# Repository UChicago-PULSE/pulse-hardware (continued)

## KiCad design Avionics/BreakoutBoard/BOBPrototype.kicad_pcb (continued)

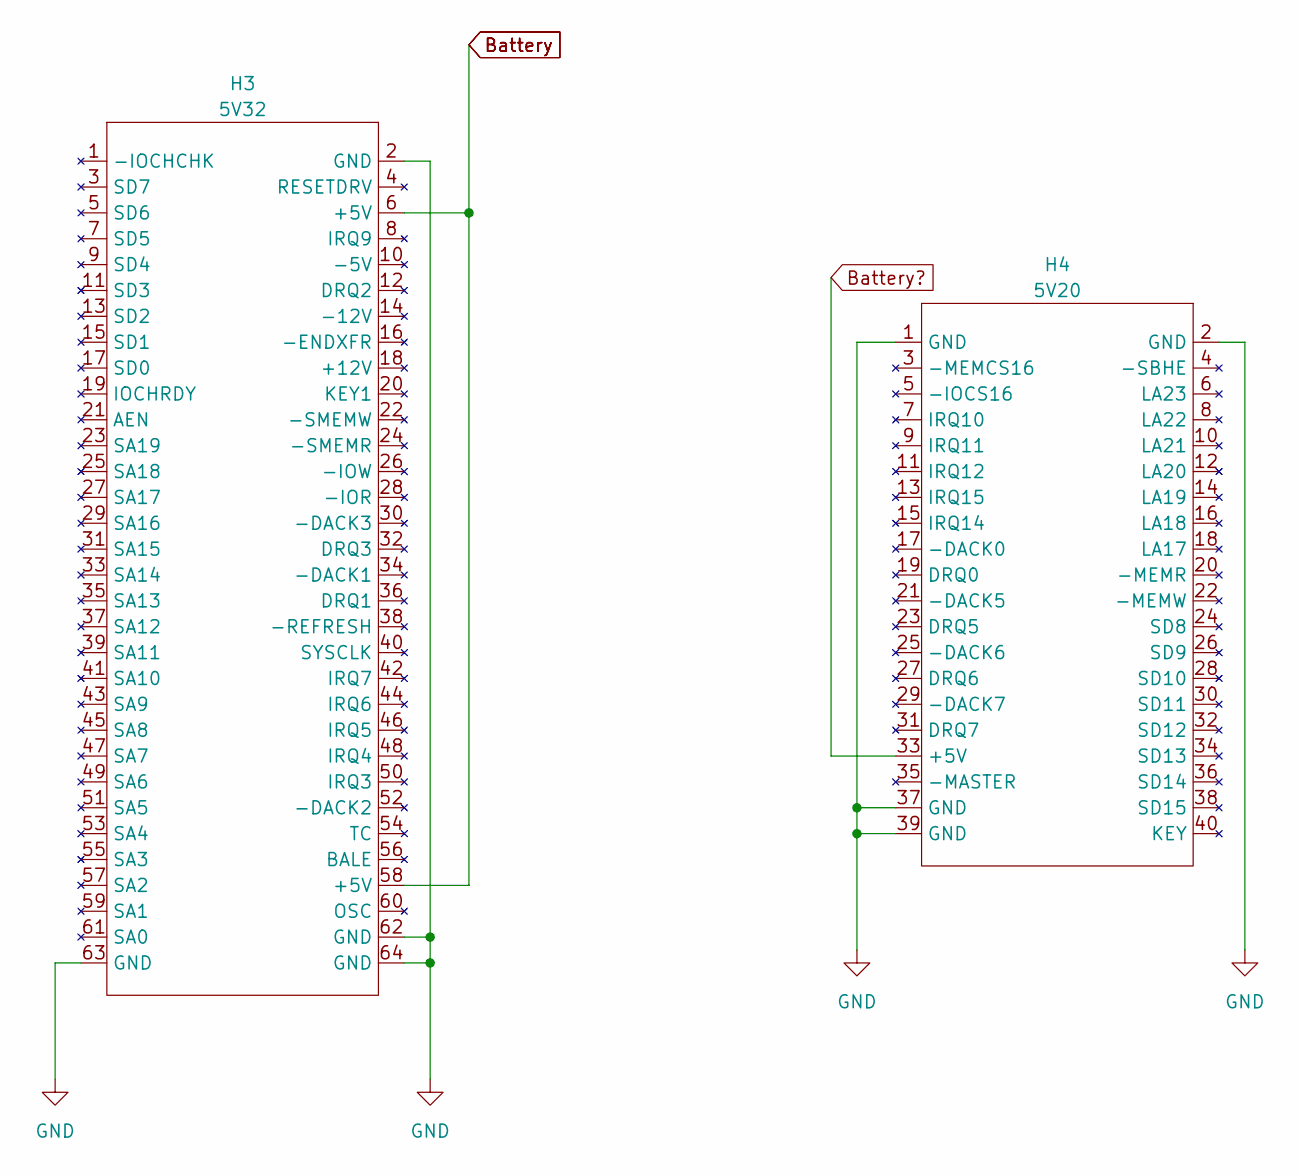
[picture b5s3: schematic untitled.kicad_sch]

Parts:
H3: 5V32
H4: 5V20

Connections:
Battery: H3.6 (+5V), H3.58 (+5V)
Battery?: H4.33 (+5V)
GND: H3.2 (GND), H3.62 (GND), H3.63 (GND), H3.64 (GND), H4.1 (GND), H4.2 (GND), H4.37 (GND), H4.39 (GND); also elsewhere on the board

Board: 2 copper layers, 9 parts (0 on the bottom side), 68 nets, no tracks yet.

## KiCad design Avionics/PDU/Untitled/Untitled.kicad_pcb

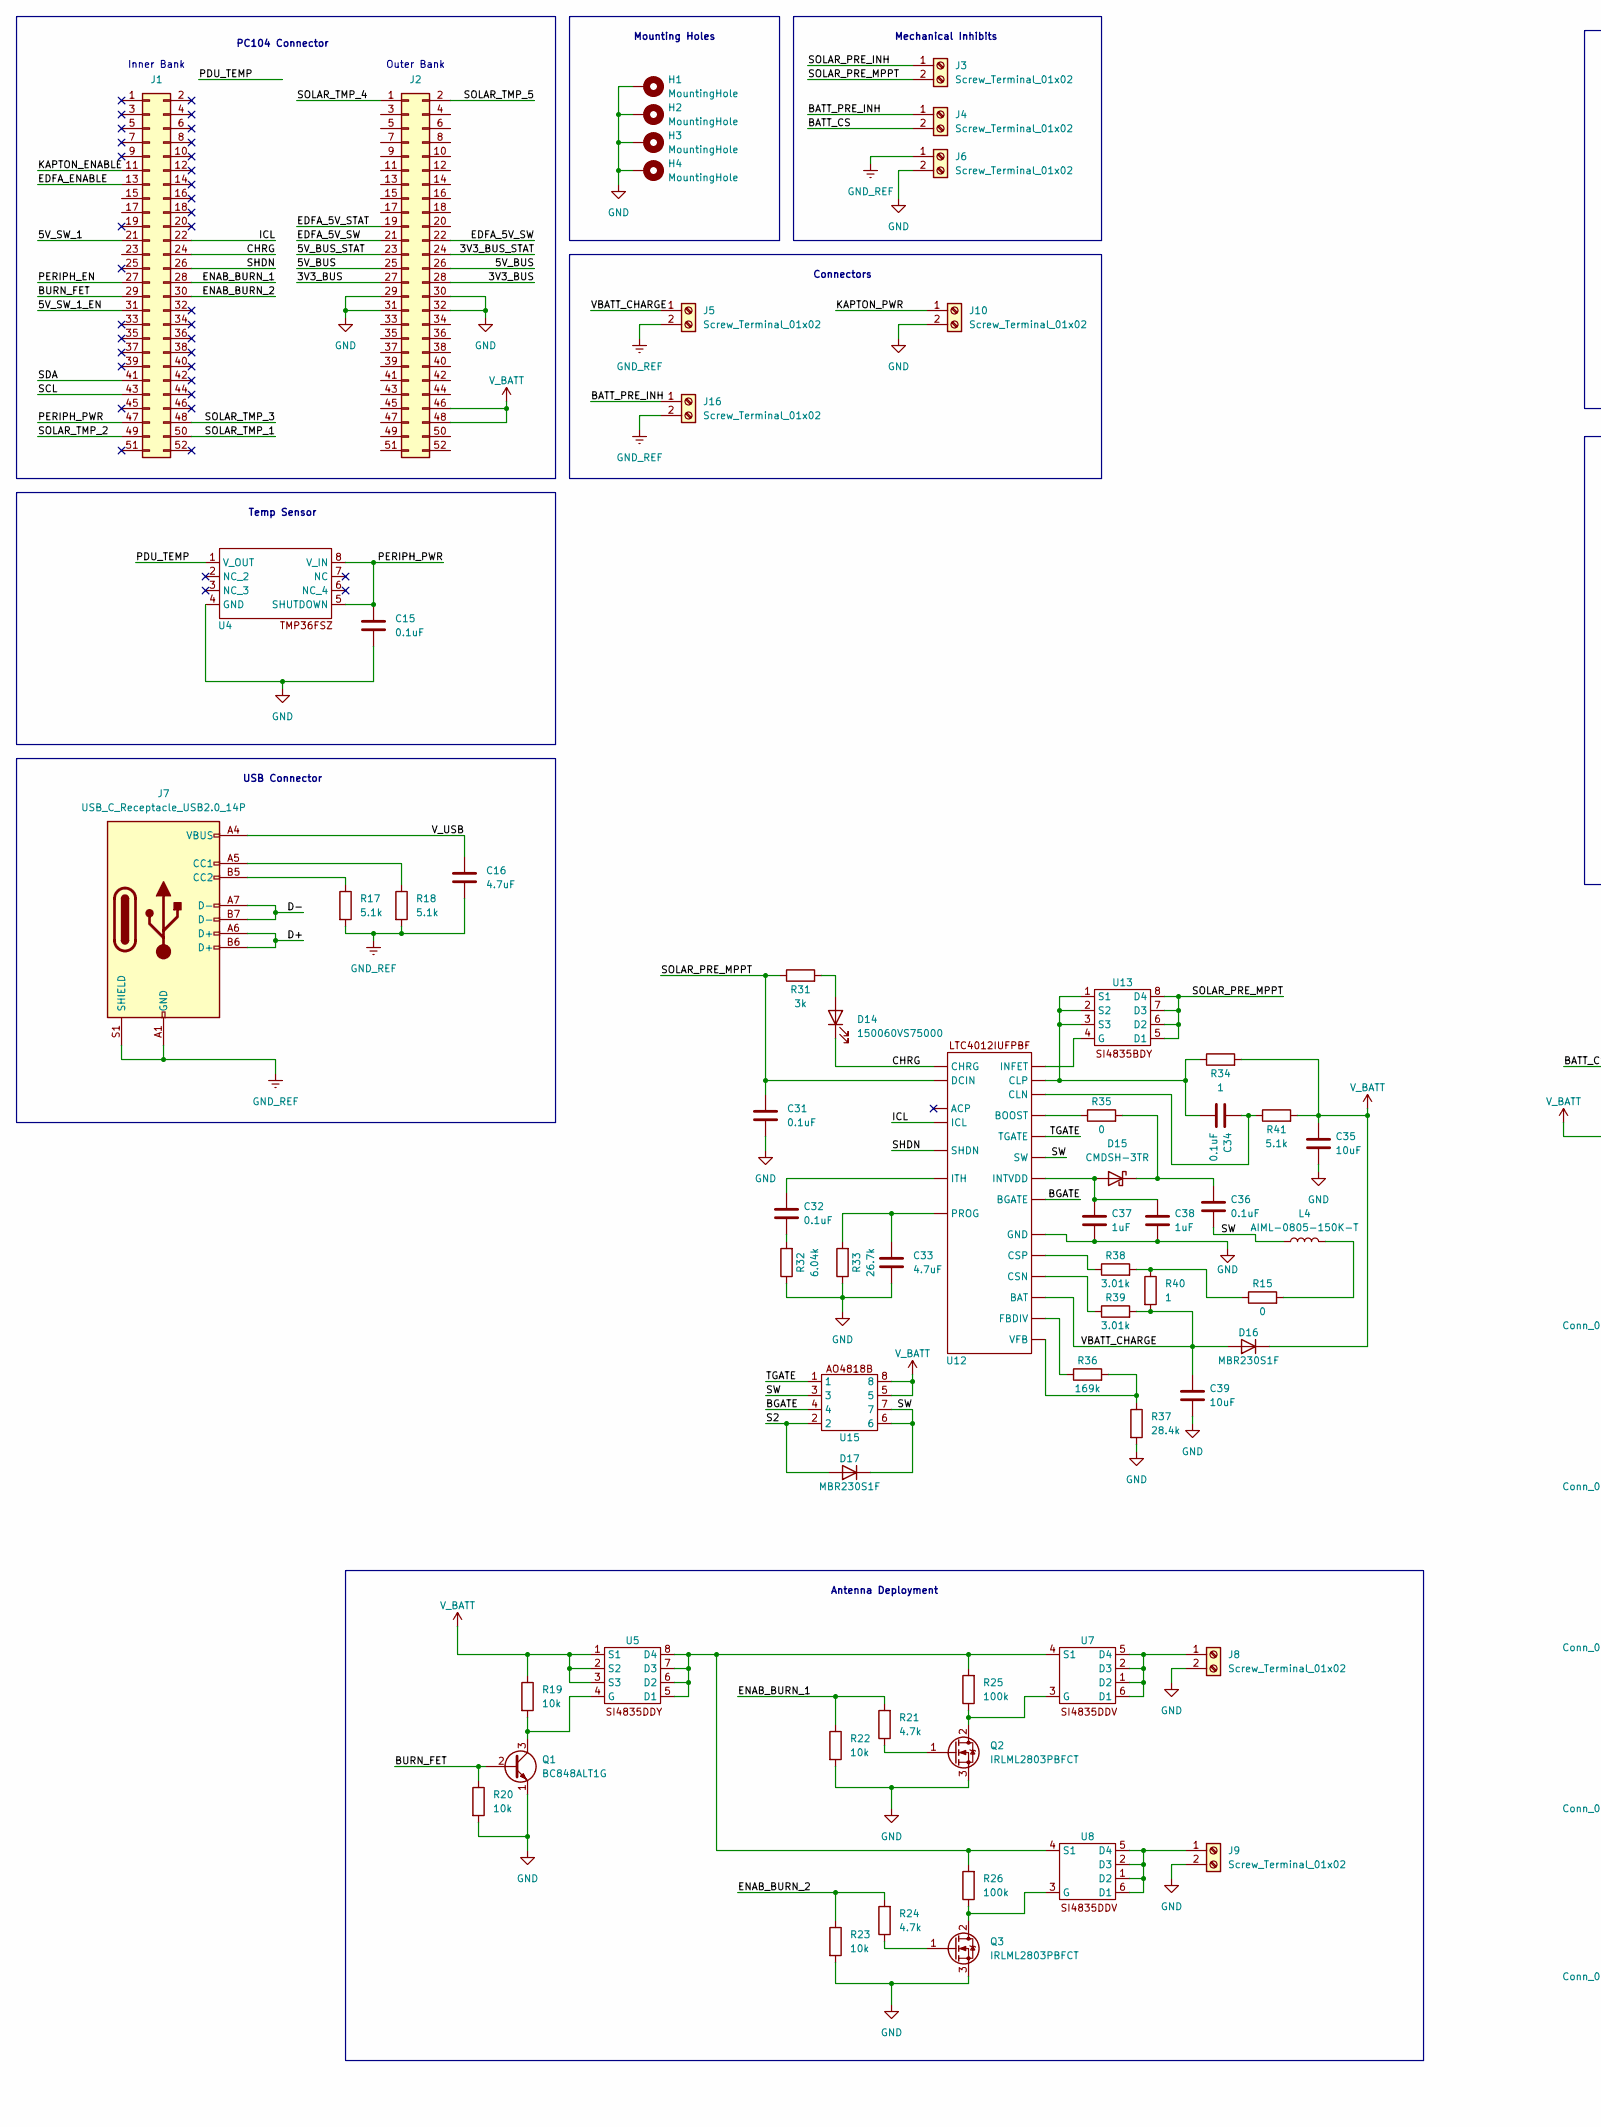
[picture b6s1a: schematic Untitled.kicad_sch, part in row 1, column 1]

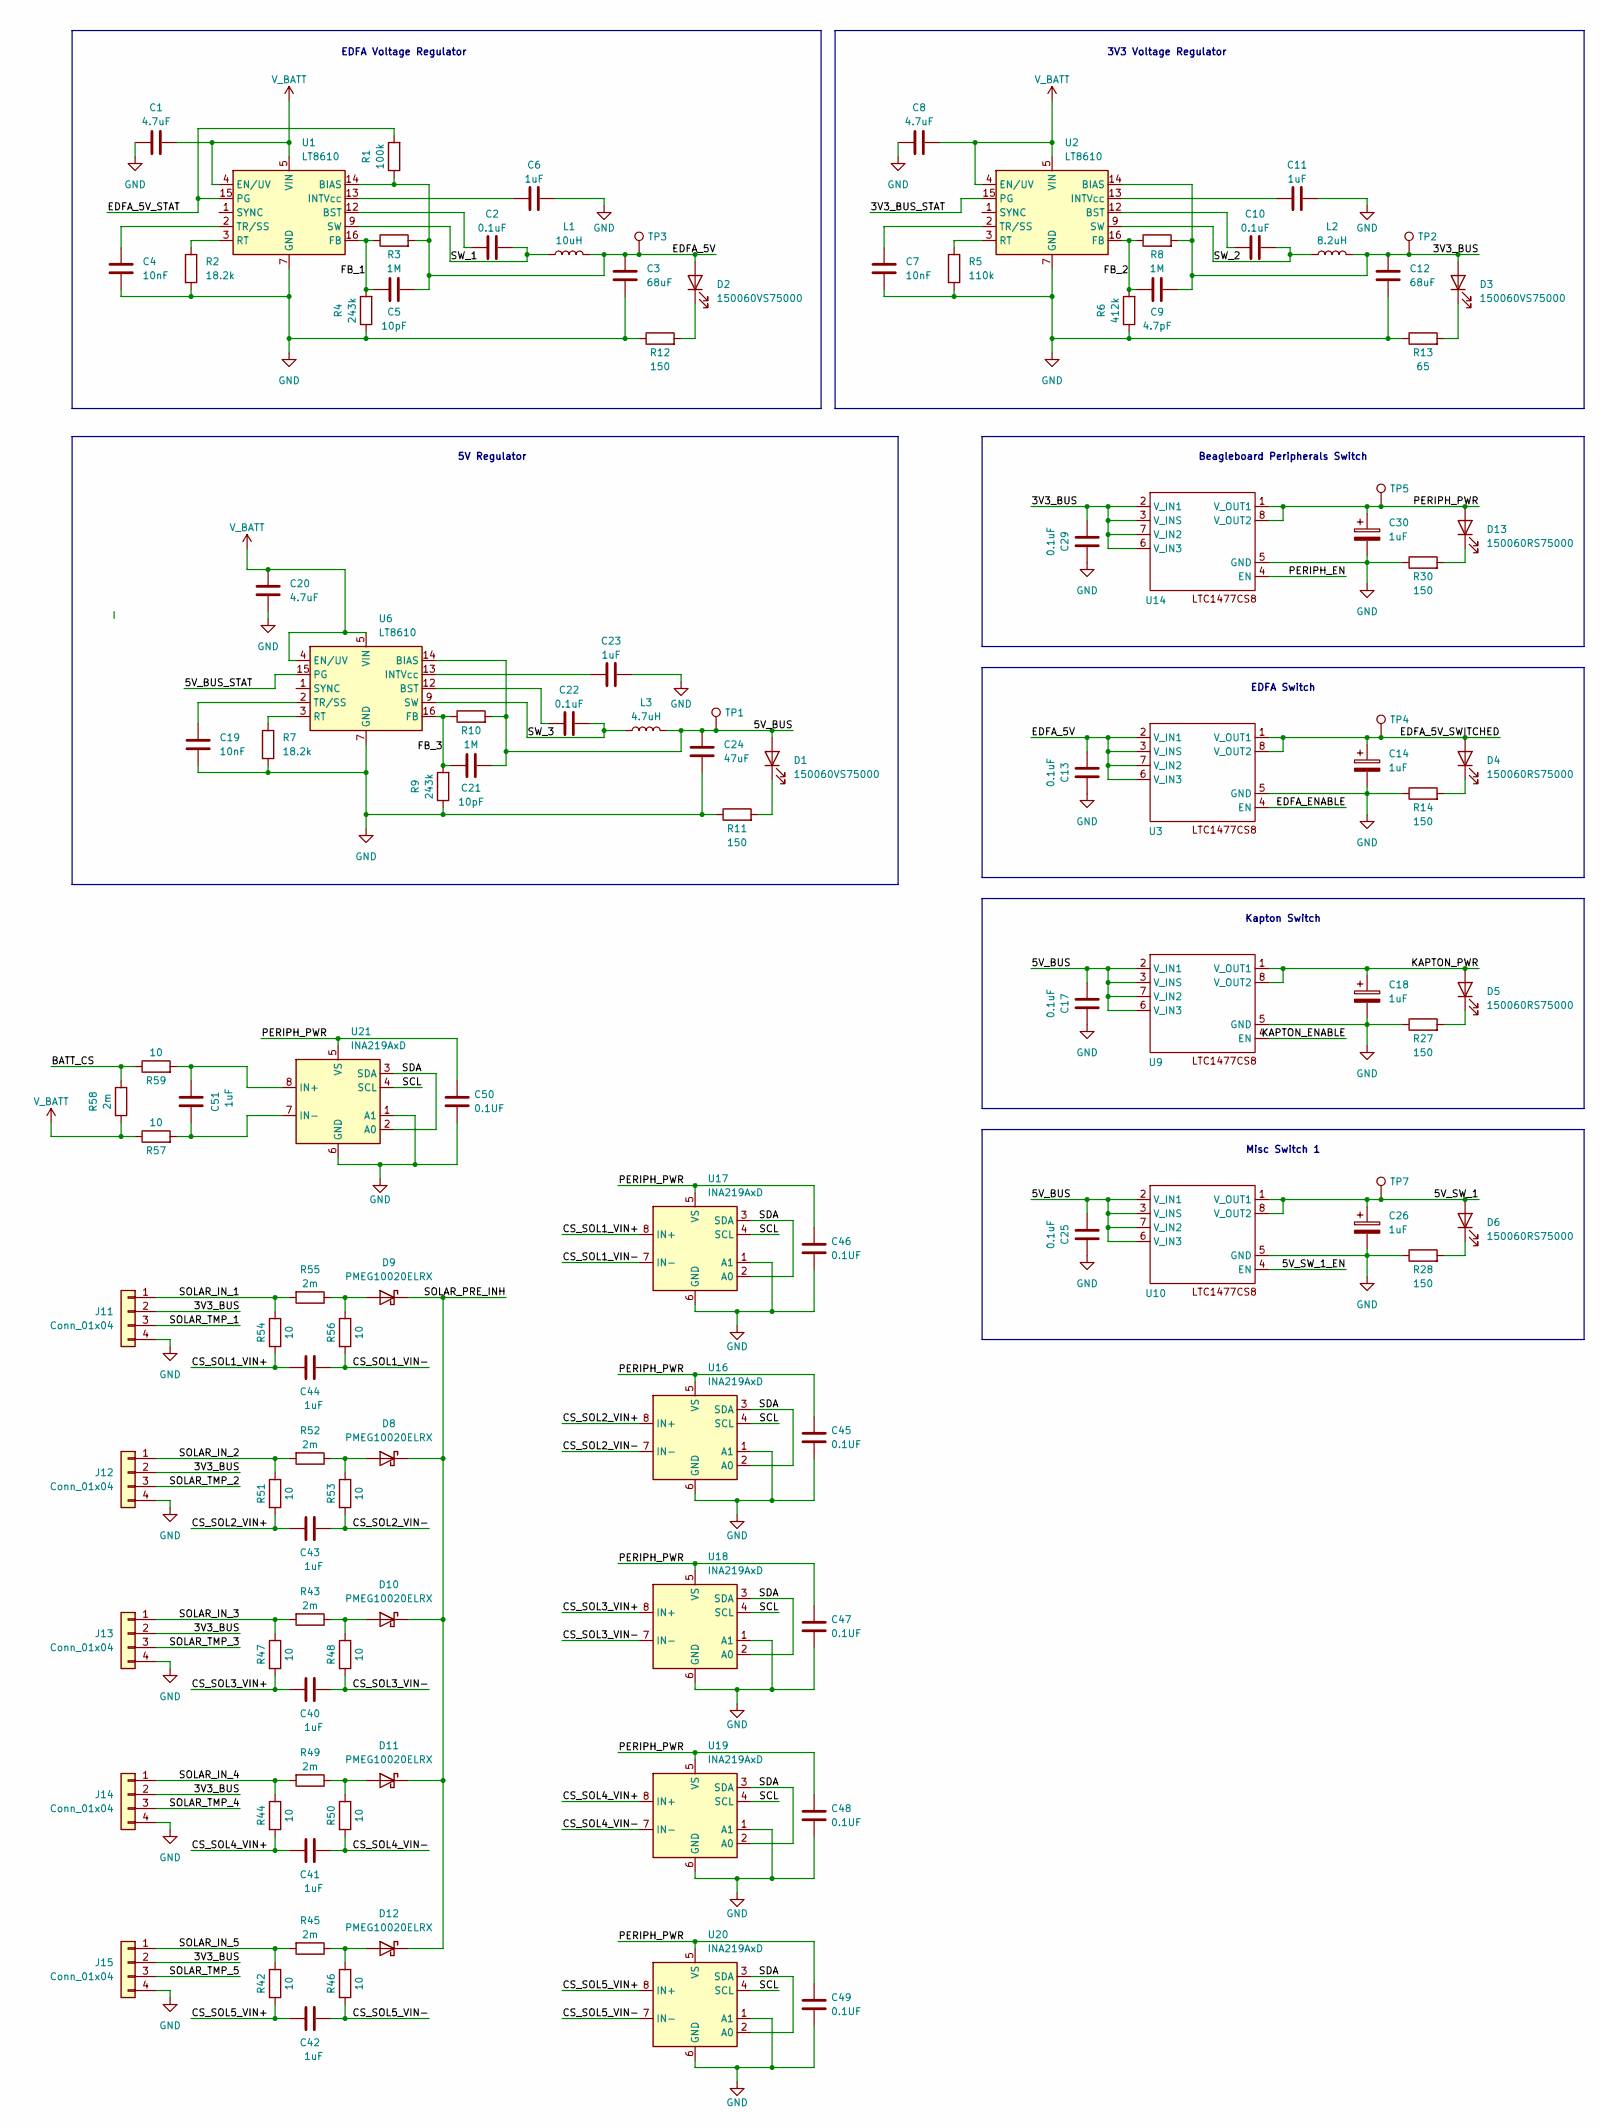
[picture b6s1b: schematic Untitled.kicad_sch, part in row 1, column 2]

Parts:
C1, C8, C20: 4.7uF; C_0402_1005Metric
C2, C10, C22, C31, C32, C34, C36: 0.1uF; C_0805_2012Metric
C3, C12: 68uF; C_0805_2012Metric
C4, C7, C19: 10nF; C_0402_1005Metric
C5, C21: 10pF; C_0805_2012Metric
C6, C11, C14, C18, C23, C26, C30: 1uF; C_0402_1005Metric
C9: 4.7pF; C_0805_2012Metric
C13, C15, C17, C25, C29: 0.1uF; C_0402_1005Metric
C16, C33: 4.7uF; C_0805_2012Metric
C24: 47uF; C_0805_2012Metric
C35, C39: 10uF; C_0805_2012Metric
C37, C38, C40, C41, C42, C43, C44, C51: 1uF; C_0805_2012Metric
C45, C46, C47, C48, C49, C50: 0.1UF; C_0402_1005Metric
D1, D2, D3, D14: 150060VS75000; LED_0603_1608Metric
D4, D5, D6, D13: 150060RS75000; LED_0603_1608Metric
D8, D9, D10, D11, D12: PMEG10020ELRX; Nexperia_CFP3_SOD-123W
D15: CMDSH-3TR; D_SOD-323F
D16, D17: MBR230S1F; D_SOD-123F
H1, H2, H3, H4: MountingHole; MountingHole_3.2mm_M3_Pad
J1, J2: Conn_02x26_Odd_Even; PinHeader_2x26_P2.54mm_Vertical
J3, J4, J5, J6, J8, J9, J10, J16: Screw_Terminal_01x02; TerminalBlock_Xinya_XY308-2.54-2P_1x02_P2.54mm_Horizontal
J7: USB_C_Receptacle_USB2.0_14P; USB_C_Receptacle_GCT_USB4105-xx-A_16P_TopMnt_Horizontal
J11, J12, J13, J14, J15: Conn_01x04; Molex_CLIK-Mate_502382-0470_1x04-1MP_P1.25mm_Vertical
L1: 10uH; L_Coilcraft_XxL4040
L2: 8.2uH; L_Coilcraft_XxL4040
L3: 4.7uH; L_Coilcraft_XxL4040
L4: AIML-0805-150K-T; L_0805_2012Metric
Q1: BC848ALT1G; SOT-23-3
Q2, Q3: IRLML2803PBFCT; SOT-23-3
R1, R25, R26: 100k; R_0805_2012Metric
R2, R7: 18.2k; C_0402_1005Metric
R3, R8, R10: 1M; R_0805_2012Metric
R4, R9: 243k; R_0805_2012Metric
R5: 110k; C_0402_1005Metric
R6: 412k; R_0805_2012Metric
R11, R12, R14, R27, R28, R30: 150; R_0603_1608Metric
R13: 65; R_0603_1608Metric
R15, R35: 0; R_0805_2012Metric
R17, R18, R41: 5.1k; R_0805_2012Metric
R19, R20, R22, R23: 10k; R_0805_2012Metric
R21, R24: 4.7k; R_0805_2012Metric
R31: 3k; R_0805_2012Metric
R32: 6.04k; R_0805_2012Metric
R33: 26.7k; R_0805_2012Metric
R34, R40: 1; R_0805_2012Metric
R36: 169k; R_0805_2012Metric
R37: 28.4k; R_0805_2012Metric
R38, R39: 3.01k; R_0805_2012Metric
R42, R44, R46, R47, R48, R50, R51, R53, R54, R56, R57, R59: 10; R_0805_2012Metric
R43, R45, R49, R52, R55, R58: 2m; R_2512_6332Metric
TP1, TP2, TP3, TP4, TP5, TP7: TestPoint_Pad_2.0x2.0mm
U1, U2, U6: LT8610; MSOP-16-1EP_3x4.039mm_P0.5mm_EP1.651x2.845mm_ThermalVias
U3, U5, U9, U10, U13, U14, U15: SOIC-8_3.9x4.9mm_P1.27mm
U4: SOIC-8-1EP_3.9x4.9mm_P1.27mm_EP2.41x3.3mm
U7, U8: TSOP-6_1.65x3.05mm_P0.95mm
U12: QFN-20-1EP_4x4mm_P0.5mm_EP2.5x2.5mm
U16, U17, U18, U19, U20, U21: INA219AxD; SOIC-8_3.9x4.9mm_P1.27mm

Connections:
/3V3_BUS: C9.2, C12.2, C29.1, D3.2 (A), J2.27, J2.28, J11.2, J12.2, J13.2, J14.2, J15.2, L2.2, R8.2, TP2.1, U2.14 (BIAS), U14.2 (V_IN1), U14.3 (V_INS), U14.6 (V_IN3), U14.7 (V_IN2)
/3V3_BUS_STAT: J2.24, U2.15 (PG)
/5V_BUS: C17.1, C21.2, C24.2, C25.1, D1.2 (A), J2.25, J2.26, L3.2, R10.2, TP1.1, U6.14 (BIAS), U9.2 (V_IN1), U9.3 (V_INS), U9.6 (V_IN3), U9.7 (V_IN2), U10.2 (V_IN1), U10.3 (V_INS), U10.6 (V_IN3), U10.7 (V_IN2)
/5V_BUS_STAT: J2.23, U6.15 (PG)
/5V_SW_1: C26.1, D6.2 (A), J1.21, TP7.1, U10.1 (V_OUT1), U10.8 (V_OUT2)
/5V_SW_1_EN: J1.31, U10.4 (EN)
/BATT_CS: J4.2, R58.1, R59.1
/BATT_PRE_INH: J4.1, J16.1
/BGATE: U12.16 (BGATE), U15.4
/BURN_FET: J1.29, Q1.2 (B), R20.1
/CHRG: D14.1 (K), J1.24, U12.7 (CHRG)
/CS_SOL1_VIN+: C44.2, R54.2, U17.8 (IN+)
/CS_SOL1_VIN-: C44.1, R56.2, U17.7 (IN-)
/CS_SOL2_VIN+: C43.2, R51.2, U16.8 (IN+)
/CS_SOL2_VIN-: C43.1, R53.2, U16.7 (IN-)
/CS_SOL3_VIN+: C40.2, R47.2, U18.8 (IN+)
/CS_SOL3_VIN-: C40.1, R48.2, U18.7 (IN-)
/CS_SOL4_VIN+: C41.2, R44.2, U19.8 (IN+)
/CS_SOL4_VIN-: C41.1, R50.2, U19.7 (IN-)
/CS_SOL5_VIN+: C42.2, R42.2, U20.8 (IN+)
/CS_SOL5_VIN-: C42.1, R46.2, U20.7 (IN-)
/D+: J7.A6 (D+), J7.B6 (D+)
/D-: J7.A7 (D-), J7.B7 (D-)
/EDFA_5V: C3.2, C5.2, C13.1, D2.2 (A), L1.2, R1.1, R3.2, TP3.1, U1.14 (BIAS), U3.2 (V_IN1), U3.3 (V_INS), U3.6 (V_IN3), U3.7 (V_IN2)
/EDFA_5V_STAT: J2.19, R1.2, U1.15 (PG)
/EDFA_5V_SW: J2.21, J2.22
/EDFA_5V_SWITCHED: C14.1, D4.2 (A), TP4.1, U3.1 (V_OUT1), U3.8 (V_OUT2)
/EDFA_ENABLE: J1.13, U3.4 (EN)
/ENAB_BURN_1: J1.28, R21.2, R22.1
/ENAB_BURN_2: J1.30, R23.1, R24.2
/FB_1: C5.1, R3.1, R4.2, U1.16 (FB)
/FB_2: C9.1, R6.2, R8.1, U2.16 (FB)
/FB_3: C21.1, R9.2, R10.1, U6.16 (FB)
/ICL: J1.22, U12.8 (ICL)
/KAPTON_ENABLE: J1.11, U9.4 (EN)
/KAPTON_PWR: C18.1, D5.2 (A), J10.1, U9.1 (V_OUT1), U9.8 (V_OUT2)
/PDU_TEMP: U4.1 (V_OUT)
/PERIPH_EN: J1.27, U14.4 (EN)
/PERIPH_PWR: C15.2, C30.1, C45.2, C46.2, C47.2, C48.2, C49.2, C50.2, D13.2 (A), J1.47, TP5.1, U4.5 (SHUTDOWN), U4.8 (V_IN), U14.1 (V_OUT1), U14.8 (V_OUT2), U16.5 (VS), U17.5 (VS), U18.5 (VS), U19.5 (VS), U20.5 (VS), U21.5 (VS)
/S2: D17.2 (A), U15.2
/SCL: J1.43, U16.4 (SCL), U17.4 (SCL), U18.4 (SCL), U19.4 (SCL), U20.4 (SCL), U21.4 (SCL)
/SDA: J1.41, U16.2 (A0), U16.3 (SDA), U17.2 (A0), U17.3 (SDA), U18.2 (A0), U18.3 (SDA), U19.2 (A0), U19.3 (SDA), U20.2 (A0), U20.3 (SDA), U21.2 (A0), U21.3 (SDA)
/SHDN: J1.26, U12.6 (SHDN)
/SOLAR_IN_1: J11.1, R54.1, R55.2
/SOLAR_IN_2: J12.1, R51.1, R52.2
/SOLAR_IN_3: J13.1, R43.2, R47.1
/SOLAR_IN_4: J14.1, R44.1, R49.2
/SOLAR_IN_5: J15.1, R42.1, R45.2
/SOLAR_PRE_INH: D8.1 (K), D9.1 (K), D10.1 (K), D11.1 (K), D12.1 (K), J3.1
/SOLAR_PRE_MPPT: C31.2, J3.2, R31.1, U12.4 (DCIN), U13.5 (D1), U13.6 (D2), U13.7 (D3), U13.8 (D4)
/SOLAR_TMP_1: J1.50, J11.3
/SOLAR_TMP_2: J1.49, J12.3
/SOLAR_TMP_3: J1.48, J13.3
/SOLAR_TMP_4: J2.1, J14.3
/SOLAR_TMP_5: J2.2, J15.3
/SW: C36.1, D17.1 (K), L4.1, U12.18 (SW), U15.3, U15.6, U15.7
/SW_1: C2.2, L1.1, U1.9 (SW), U1.10 (SW), U1.11 (SW)
/SW_2: C10.2, L2.1, U2.9 (SW), U2.10 (SW), U2.11 (SW)
/SW_3: C22.2, L3.1, U6.9 (SW), U6.10 (SW), U6.11 (SW)
/TGATE: U12.19 (TGATE), U15.1
/VBATT_CHARGE: C39.2, D16.2 (A), J5.1, R39.2, R40.2, U12.11 (BAT)
/V_USB: C16.2, J7.A4 (VBUS), J7.A9 (VBUS), J7.B4 (VBUS), J7.B9 (VBUS)
GND: C1.1, C3.1, C4.1, C6.2, C7.1, C8.1, C11.2, C12.1, C13.2, C14.2, C15.1, C17.2, C18.2, C19.1, C20.1, C23.2, C24.1, C25.2, C26.2, C29.2, C30.2, C31.1, C33.1, C35.1, C37.1, C38.1, C39.1, C45.1, C46.1, C47.1, C48.1, C49.1, C50.1, H1.MP, H2.MP, H3.MP, H4.MP, J2.29, J2.30, J2.31, J2.32, J6.2, J8.2, J9.2, J10.2, J11.4, J12.4, J13.4, J14.4, J15.4, Q1.1 (E), Q2.3 (S), Q3.3 (S), R2.2, R4.1, R5.2, R6.1, R7.2, R9.1, R11.1, R12.1, R13.1, R14.1, R20.2, R22.2, R23.2, R27.1, R28.1, R30.1, R32.1, R33.1, R37.2, U1.7 (GND), U1.8 (GND), U1.17 (GND), U2.7 (GND), U2.8 (GND), U2.17 (GND), U3.5 (GND), U4.4 (GND), U6.7 (GND), U6.8 (GND), U6.17 (GND), U9.5 (GND), U10.5 (GND), U12.21 (GND), U14.5 (GND), U16.1 (A1), U16.6 (GND), U17.1 (A1), U17.6 (GND), U18.1 (A1), U18.6 (GND), U19.1 (A1), U19.6 (GND), U20.1 (A1), U20.6 (GND), U21.1 (A1), U21.6 (GND)
GND_REF: C16.1, J5.2, J6.1, J7.A1 (GND), J7.A12 (GND), J7.B1 (GND), J7.B12 (GND), J7.S1 (SHIELD), J16.2, R17.2, R18.2
unnamed: C32.1, R32.2
unnamed: D1.1 (K), R11.2
unnamed: D2.1 (K), R12.2
unnamed: D3.1 (K), R13.2
unnamed: D4.1 (K), R14.2
unnamed: D5.1 (K), R27.2
unnamed: D6.1 (K), R28.2
unnamed: D8.2 (A), R52.1, R53.1
unnamed: D9.2 (A), R55.1, R56.1
unnamed: D10.2 (A), R43.1, R48.1
unnamed: D11.2 (A), R49.1, R50.1
unnamed: D12.2 (A), R45.1, R46.1
unnamed: D13.1 (K), R30.2
unnamed: D14.2 (A), R31.2
unnamed: C37.2, C38.2, D15.2 (A), U12.17 (INTVDD)
unnamed: C36.2, D15.1 (K), R35.2
unnamed: J7.A5 (CC1), R18.1
unnamed: J7.B5 (CC2), R17.1
unnamed: J8.1, U7.1 (D2), U7.2 (D3), U7.5 (D4), U7.6 (D1)
unnamed: J9.1, U8.1 (D2), U8.2 (D3), U8.5 (D4), U8.6 (D1)
unnamed: L4.2, R15.2
unnamed: Q1.3 (C), R19.2, U5.4 (G)
unnamed: Q2.2 (D), R25.1, U7.3 (G)
unnamed: Q2.1 (G), R21.1
unnamed: Q3.2 (D), R26.1, U8.3 (G)
unnamed: Q3.1 (G), R24.1
unnamed: R15.1, R38.2, R40.1
unnamed: C2.1, U1.12 (BST)
unnamed: C6.1, U1.13 (INTVcc)
unnamed: R2.1, U1.3 (RT)
unnamed: C4.2, U1.2 (TR/SS)
unnamed: C10.1, U2.12 (BST)
unnamed: C11.1, U2.13 (INTVcc)
unnamed: R5.1, U2.3 (RT)
unnamed: C7.2, U2.2 (TR/SS)
unnamed: R25.2, R26.2, U5.5 (D1), U5.6 (D2), U5.7 (D3), U5.8 (D4), U7.4 (S1), U8.4 (S1)
unnamed: C22.1, U6.12 (BST)
unnamed: C23.1, U6.13 (INTVcc)
unnamed: R7.1, U6.3 (RT)
unnamed: C19.2, U6.2 (TR/SS)
unnamed: R35.1, U12.20 (BOOST)
unnamed: C34.2, R41.1, U12.1 (CLN)
unnamed: C34.1, R34.1, U12.2 (CLP), U13.1 (S1), U13.2 (S2), U13.3 (S3)
unnamed: R39.1, U12.14 (CSN)
unnamed: R38.1, U12.15 (CSP)
unnamed: R36.1, U12.10 (FBDIV)
unnamed: U12.3 (INFET), U13.4 (G)
unnamed: C32.2, U12.12 (ITH)
unnamed: C33.2, R33.2, U12.13 (PROG)
unnamed: R36.2, R37.1, U12.9 (VFB)
unnamed: C51.1, R59.2, U21.8 (IN+)
unnamed: C51.2, R57.2, U21.7 (IN-)
V_BATT: C1.2, C8.2, C20.2, C35.2, D16.1 (K), J2.46, J2.48, R19.1, R34.2, R41.2, R57.1, R58.2, U1.4 (EN/UV), U1.5 (VIN), U1.6 (VIN), U2.4 (EN/UV), U2.5 (VIN), U2.6 (VIN), U5.1 (S1), U5.2 (S2), U5.3 (S3), U6.4 (EN/UV), U6.5 (VIN), U6.6 (VIN), U15.5, U15.8

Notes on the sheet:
PC104 Connector
5V Regulator
Temp Sensor
Kapton Switch
3V3 Voltage Regulator
Beagleboard Peripherals Switch
Outer Bank
Inner Bank
USB Connector
Antenna Deployment
EDFA Switch
Misc Switch 1
Mechanical Inhibits
EDFA Voltage Regulator
Connectors
Mounting Holes

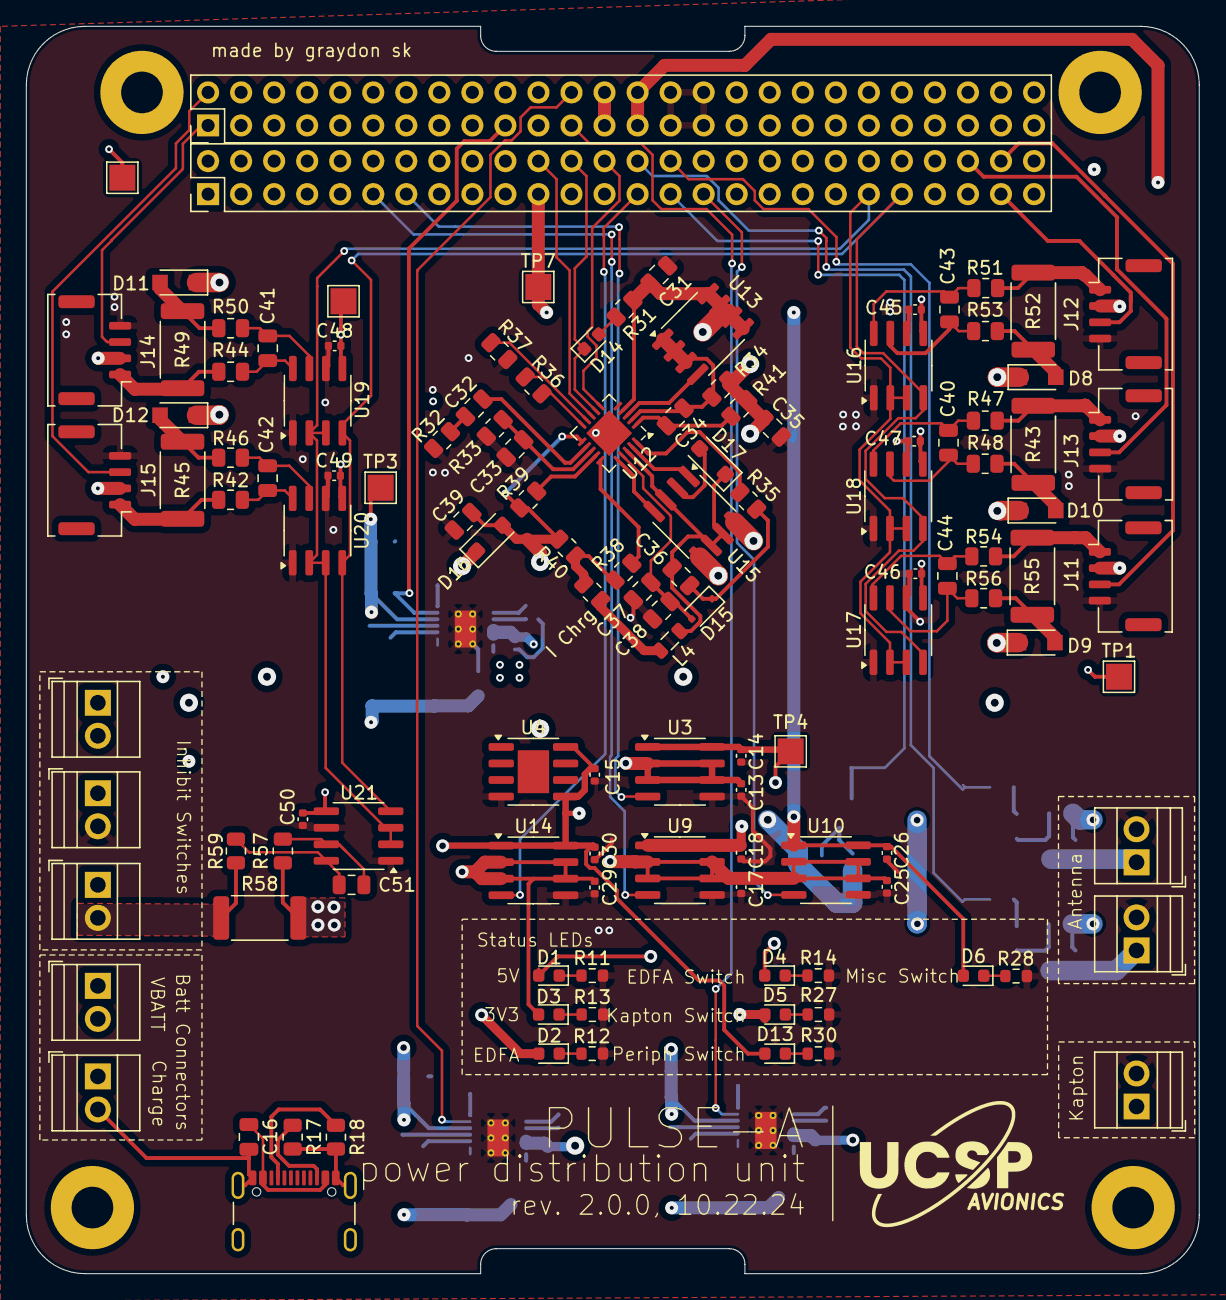
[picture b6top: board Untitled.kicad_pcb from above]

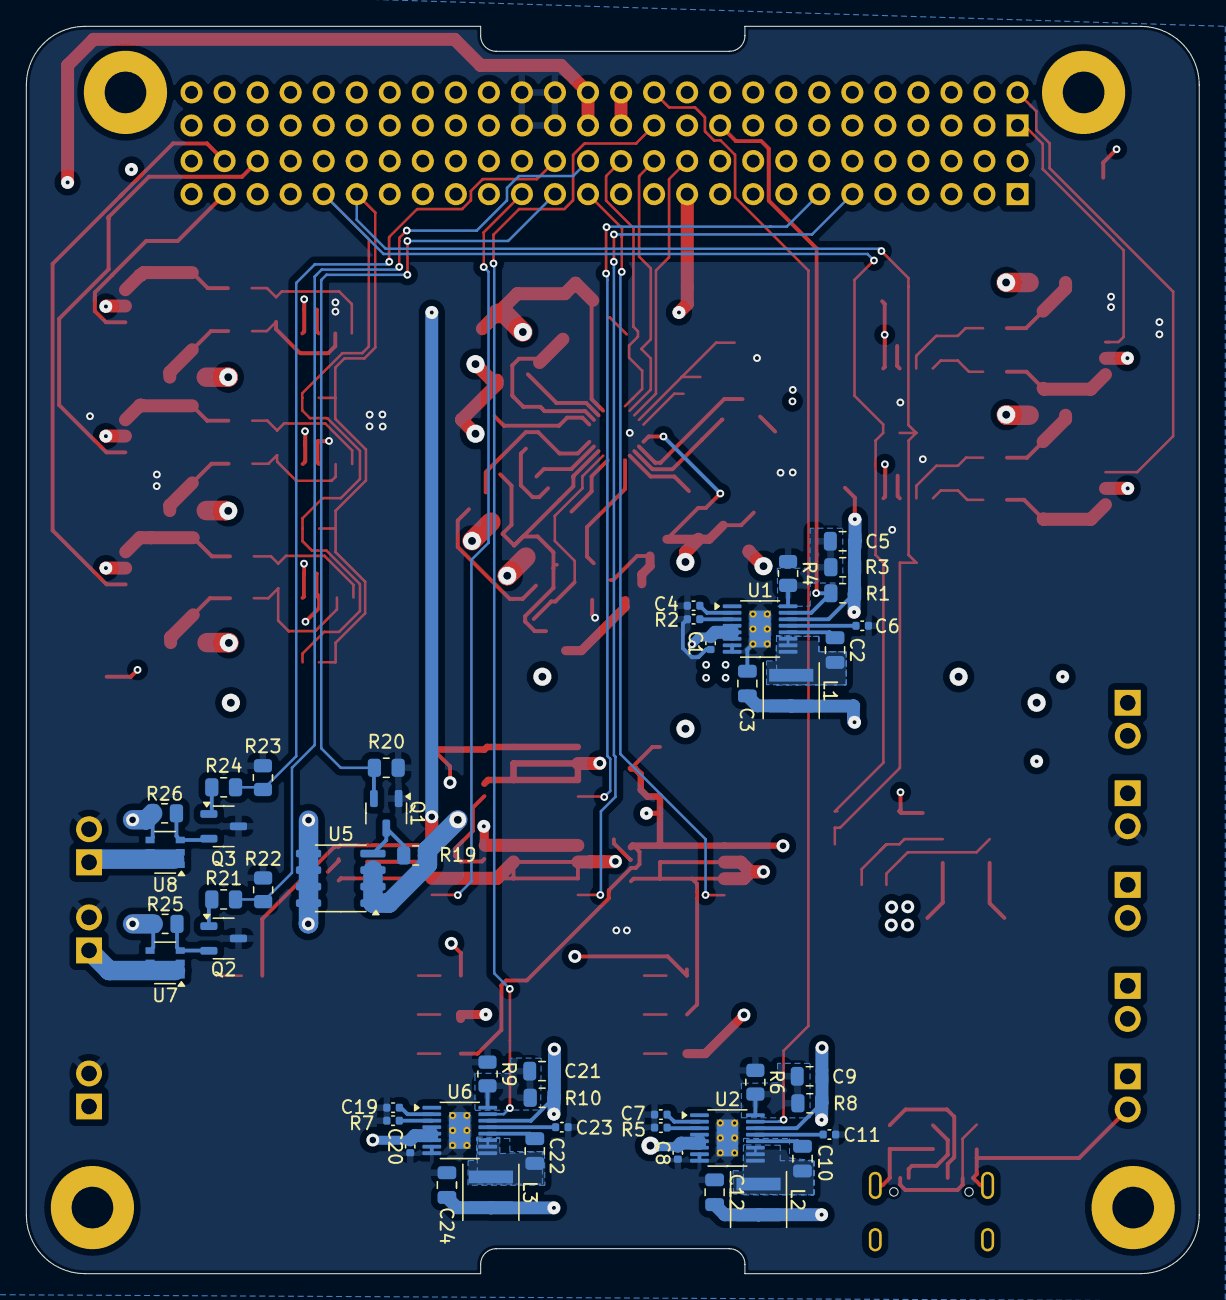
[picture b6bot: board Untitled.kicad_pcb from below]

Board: 4 copper layers, 90.2 x 95.9 mm, 175 parts (48 on the bottom side), 116 nets.
